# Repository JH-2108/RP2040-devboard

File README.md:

# Small devboard 

A custom RP2040-based development board designed from scratch in KiCAD as part of Hack Club Half Life. 

The DevBoard is a compact general-purpose development platform with native USB-C connectivity, external QSPI flash, 3.3V power regulation, GPIO breakout, onboard controls, and a status LED. The board is intended to be used for embedded programming, electronics experimentation, robotics, sensors, displays, and future hardware projects. 

# Features 
- Raspberry Pi RP2040 microcontroller
- Native USB-C connectivity
- External QSPI flash
- 12 MHz crystal oscillator
- 3.3V power regulation
- 2x20 GPIO breakout pins
- BOOTSEL and RESET buttons
- Onboard status LED
- SMD components
- Custom PCB designed in KiCAD

# Hardware 
The board is built around the RP2040 and follows the required circuity for its power, clock, USB, and external flash interfaces. 

# Main components
- RP2040 MCU
- W25Q128 QSPI flash
- 12 MHz crystal
- USB-C connector
- 3.3V LDO regulator
- Decoupling and filtering capacitors
- USB-C CC resistors
- GPIO headers
- RESET and BOOTSEL buttons
- Status LED

# Firmware
The devboard will be programmed using the Raspberry Pi Pico SDK and C/C++. 

The initial firmware will provide: 
- RP2040 boot and initialization
- USB connectivity
- GPIO testing
- Status LED control
- Board diagnostics
- USB serial communication

A diagnostic firmware can be used to verify that the assembled PCB is functioning correctly. 

# PC software
A small optional Python utility may be developed to communicated with the board over USB serial. 

This can be used to 
- Display board information
- Run hardware tests
- Control the onboard LED
- Test GPIO
- Monitor diagnostic output

# Firmware flashing 
The devboard uses the RP2040 microcontroller chip. Compatible UF2 firmware can be flashed over USB without an external programmer, provided the board's USB interface and BOOTSEL circuit are functioning correctly. 

# Requirements
- A USB data cable compatible with the board's USB-C connector
- A computer running either Windows, macOS, or Linux
- A compatible .uf2 firmware file

# Instructions 
1. Obtain the firmware. Download a UF2 firmware file that is compatible with the RP2040 and the intended application. Alternatively, build the firmware from its source code using the appropriate development tools.
2. Enter BOOTSEL mode. Disconnect the devboard from USB. Press and hold the BOOTSEL button, then connect the board to the computer. Release the button after the computer detects the board.
3. Open the bootloader drive. The board should appear as a USB mass-storage device named RPI-RP2. If it does not appear, check the connecting cable, power supply, and BOOTSEL circuit.
4. Copy the firmware. Drag the compatible .uf2 file into the RPI-RP2 drive.
5. Wait for the installation to finish. The drive should disconnect automatically as the RP2040 reboots and begins running the newly installed firmware.
6. Test the board. Verify that the firmware behaves as expected. If the application exposes a USB serial interface, open a serial terminal to inspect its output.

# Troubleshooting 
- The drive does not appear: make sure your USB cable supports data, not just charging. Check that the board receives power and the BOOTSEL circuit is assembled correctly.
- The firmware is rejected or does not run: confirm that the UF2 file targets the RP2040 and is built for the board's memory layout and hardware.
- The board does not behave as expected: try a known-compatible firmware image and inspect the power supply, clock circuit (especially this one), flash connections, and USB data routing.

# Important Notes 
- A UF2 file must be compatible with the RP2040 and the target firmware cofiguration.
- Flashing new firmware replaces the existing application in flash memory.
- BOOTSEL mode is implemented in the RP2040's read-only boot ROM, so compatible hardware can normally re-enter the bootloader even if the installed application fails.
If all else does not work, see the official Raspberry Pi microcontroller chip documentation. 

# Design
The PCB and schematic are designed using KiCAD. 
Project files include: 
- Schematic
- PCB layout
- Component/footprint assignments
- BOM
- Manufacturing files

# Design process
1. select and verify components for pricing and whether it is within budget range
2. create the schematic
3. assign symbols and footprints
4. design the PCB layout
5. route the board
6. run electrical and design rule checks
7. generate gerber files
8. assemble the PCB
9. develop and test firmware
10. test the complete board

# Bill of Materials 
|Item|Qty                          |Supplier|Cost/item                                    |Total Cost|link                                                                                                                                                                                                                                               |
|----|-----------------------------|--------|---------------------------------------------|----------|---------------------------------------------------------------------------------------------------------------------------------------------------------------------------------------------------------------------------------------------------|
|Raspberry Pi RP2040CT|1                            |Cytron  |$1.15                                        |$1.15     |https://my.cytron.io/p-raspberry-pi-rp2040-mcu-ic-single-unit                                                                                                                                                                                      |
|Winbond W25Q128JVSIQ|1                            |LCSC    |$2.52                                        |$2.52     |https://www.lcsc.com/product-detail/C113767.html                                                                                                                                                                                                   |
|12 MHz SMD crystal, 3225 4-pin|5                            |LCSC    |$0.10                                        |$0.50     |https://www.lcsc.com/product-detail/C518158.html                                                                                                                                                                                                   |
|USB Type-C 16-pin receptacle|1                            |Shopee Malaysia|$0.65                                        |$0.65     |https://shopee.com.my/Type-C-3.1-Patch-Socket-6P-16P-24P-Countersunk-Board-1.6-0.8mm-USB-Female-Socket-Data-Interface-i.513412485.42610897264?extraParams=%7B%22display_model_id%22%3A260916036060%2C%22model_selection_logic%22%3A3%7D            |
|3.3 V LDO regulator|1                            |Shopee Malaysia|$0.46                                        |$0.46     |https://shopee.com.my/AMS1117-Voltage-Regulator-IC-SOT-223-1.2V-1.5V-1.8V-2.5V-3.3V-5V-i.1412281456.49416215365?extraParams=%7B%22display_model_id%22%3A396380238012%2C%22model_selection_logic%22%3A3%7D                                          |
|10 µF ceramic capacitor|1                            |Shopee Malaysia|$1.05                                        |$1.05     |https://shopee.com.my/50V-10uF-Multilayer-Capacitor-i.40459773.23082863550?extraParams=%7B%22display_model_id%22%3A138766713726%2C%22model_selection_logic%22%3A3%7D                                                                               |
|100 nF ceramic capacitor|1                            |Shopee Malaysia|$1.25                                        |$1.25     |https://shopee.com.my/0402-0603-0805-1206-100nF-820nF-SMD-Chip-Capacitor-i.1467039591.41834021222?extraParams=%7B%22display_model_id%22%3A218871594639%2C%22model_selection_logic%22%3A3%7D                                                        |
|5.1 kΩ resistor|1                            |Shopee Malaysia|$1.24                                        |$1.24     |https://shopee.com.my/SMD-0402-0603-0805-1206-RESISTOR-1K-9.1K-Ohm-i.1467039591.50009312017?extraParams=%7B%22display_model_id%22%3A307560786040%2C%22model_selection_logic%22%3A3%7D                                                              |
|1 kΩ resistor|1                            |Shopee Malaysia|$1.24                                        |$1.24     |https://shopee.com.my/SMD-0402-0603-0805-1206-RESISTOR-1K-9.1K-Ohm-i.1467039591.50009312017?extraParams=%7B%22display_model_id%22%3A307560786040%2C%22model_selection_logic%22%3A3%7D                                                              |
|0603 LED|1                            |Shopee Malaysia|$0.88                                        |$0.88     |https://shopee.com.my/SMD-0402-0603-0805-1206-RESISTOR-1K-9.1K-Ohm-i.1467039591.50009312017?extraParams=%7B%22display_model_id%22%3A307560786040%2C%22model_selection_logic%22%3A3%7D                                                              |
|Tactile push button|1                            |Shopee Malaysia|$0.31                                        |$0.31     |https://shopee.com.my/Button-Switch-Tactile-Push-6x6x5mm-6*6*5mm-4PIN-i.482535902.11217352127?extraParams=%7B%22display_model_id%22%3A100951846821%2C%22model_selection_logic%22%3A3%7D                                                            |
|Tactile push button|1                            |Shopee Malaysia|$0.31                                        |$0.31     |https://shopee.com.my/Button-Switch-Tactile-Push-6x6x5mm-6*6*5mm-4PIN-i.482535902.11217352127?extraParams=%7B%22display_model_id%22%3A100951846821%2C%22model_selection_logic%22%3A3%7D                                                            |
|2.54 mm male pin headers|1                            |Shopee Malaysia|$0.30                                        |$0.30     |https://shopee.com.my/Male-Header-Pins-Straight-Single-Row-40-Pin-0.1-Inch-(2.54mm)-Male-Pin-Header-Connector-PCB-Board-Pin-Connect-i.161803224.7025057004?extraParams=%7B%22display_model_id%22%3A21946244149%2C%22model_selection_logic%22%3A3%7D|
|Custom PCB|1                            |JLCPCB  |$5.78                                        |$5.78     |https://jlcpcb.com                                                                                                                                                                                                                                 |
|Estimated total shipping|1                            |        |                                             |$7.75     |                                                                                                                                                                                                                                                   
# Project goals
The main goal is to design and build a fully functioning custom development board rather than relying on an existing development board such as the Raspberry Pi Pico. 

The project combines: 
- PCB design
- embedded systems
- electronics
- Firmware development
- USB communication
- hardware testing
- software development

# project images

**Schematic** 

**PCB layout**

**3d Render**

**Finished PCB**
a photo will be added here 

# LICENSE
This project is licensed under MIT License, check out [LICENSE](LICENSE) for more details.

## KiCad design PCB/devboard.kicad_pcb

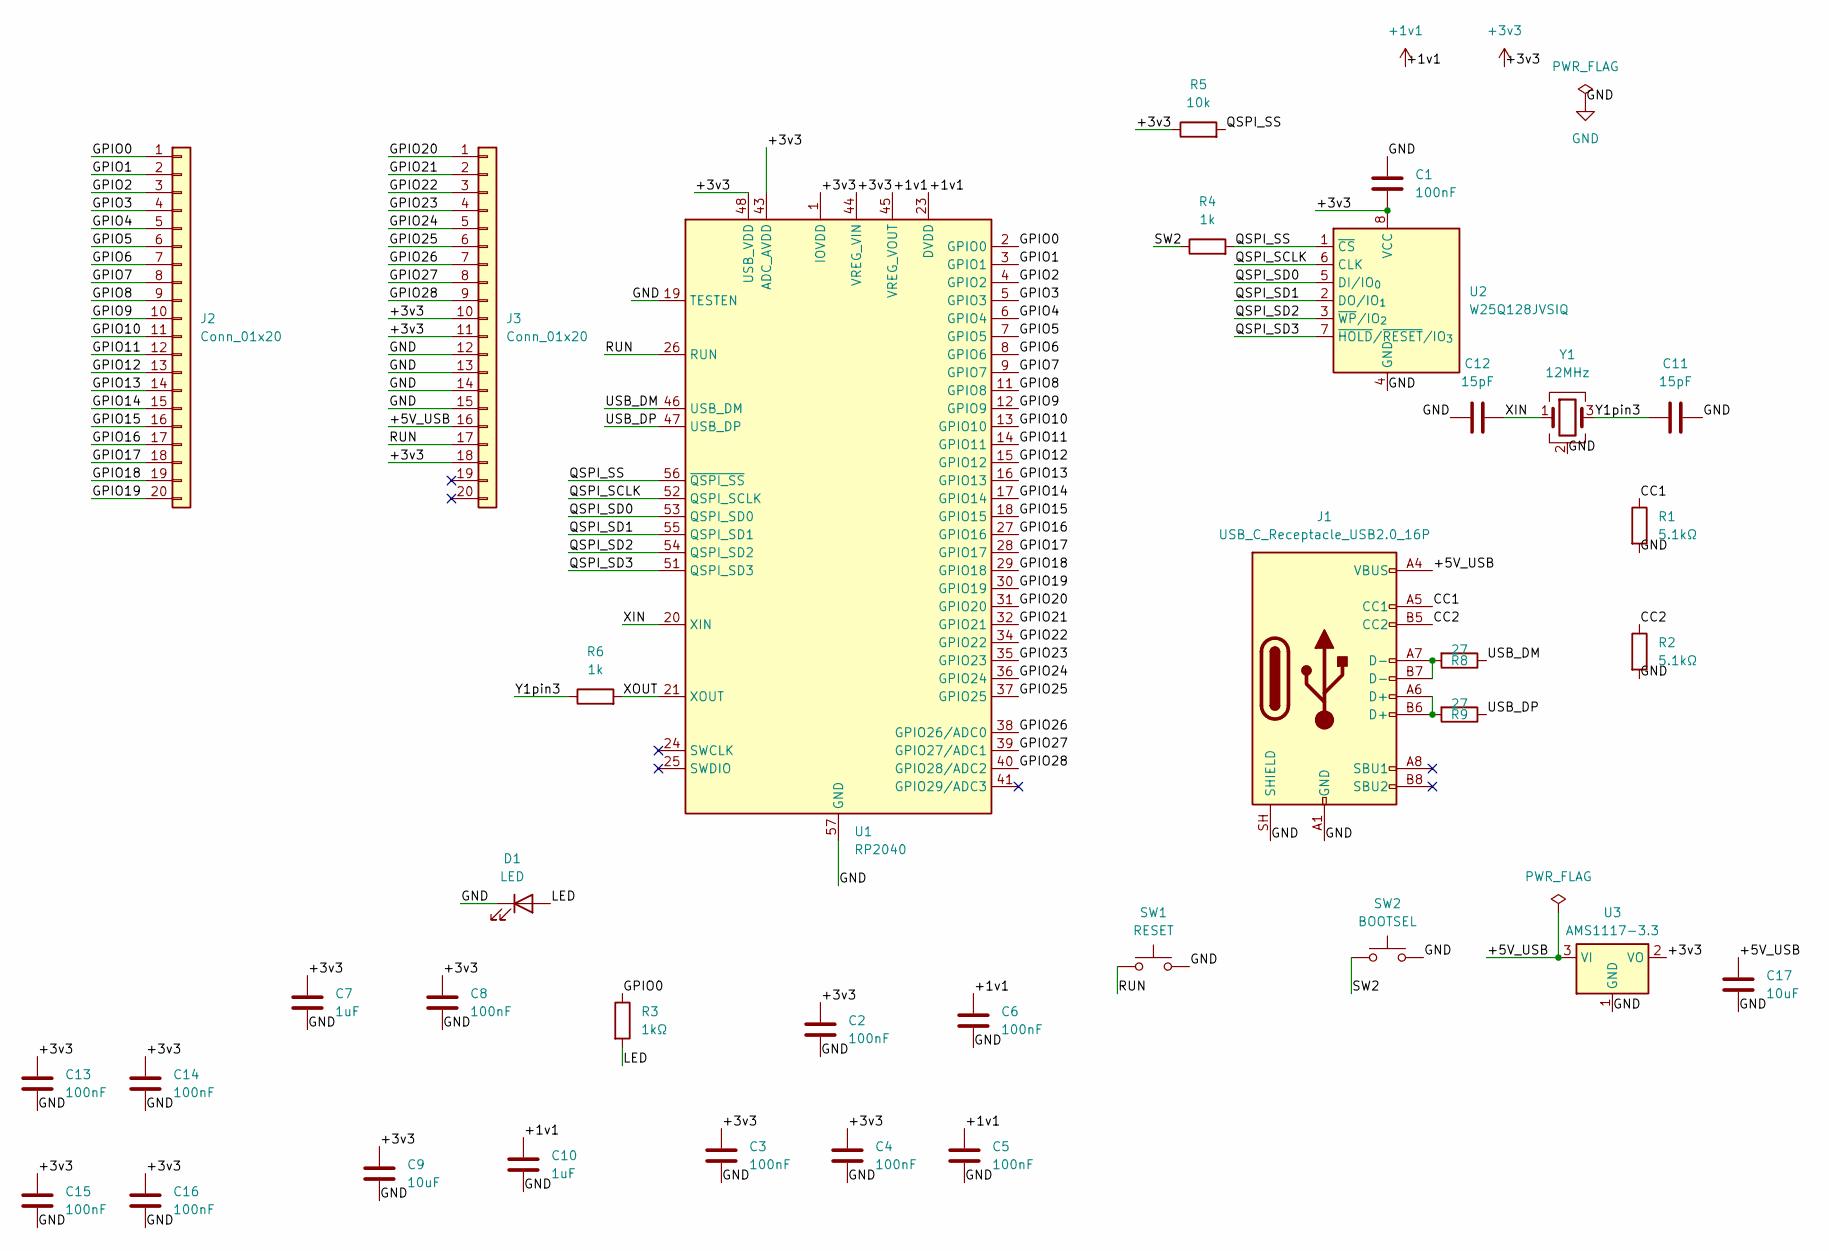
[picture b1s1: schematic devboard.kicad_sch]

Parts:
C1, C2, C3, C4, C5, C6, C8, C13, C14, C15, C16: 100nF; C_0603_1608Metric
C7, C10: 1uF; C_0603_1608Metric
C9, C17: 10uF; C_0603_1608Metric
C11, C12: 15pF; C_0603_1608Metric
D1: LED; LED_0603_1608Metric
J1: USB_C_Receptacle_USB2.0_16P; USB_C_Receptacle_GCT_USB4105-xx-A_16P_TopMnt_Horizontal
J2, J3: Conn_01x20; PinHeader_1x20_P2.54mm_Vertical
R1, R2: 5.1kΩ; R_0603_1608Metric
R3: 1kΩ; R_0603_1608Metric
R4, R6: 1k; R_0603_1608Metric
R5: 10k; R_0603_1608Metric
R8, R9: 27; R_0603_1608Metric
SW1: RESET; SW_Push_1P1T_NO_E-Switch_TL3301NxxxxxG
SW2: BOOTSEL; SW_Push_1P1T_NO_E-Switch_TL3301NxxxxxG
U1: RP2040; QFN-56-1EP_7x7mm_P0.4mm_EP3.2x3.2mm
U2: W25Q128JVSIQ; SOIC-8_5.3x5.3mm_P1.27mm
U3: AMS1117-3.3; SOT-223-3_TabPin2
Y1: 12MHz; Crystal_SMD_3225-4Pin_3.2x2.5mm

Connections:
+1v1: C5.1, C6.1, C10.1, U1.23 (DVDD), U1.45 (VREG_VOUT), U1.50 (DVDD)
+3v3: C1.2, C2.1, C3.1, C4.1, C7.1, C8.1, C9.1, C13.1, C14.1, C15.1, C16.1, J3.10, J3.11, J3.18, R5.1, U1.1 (IOVDD), U1.10 (IOVDD), U1.22 (IOVDD), U1.33 (IOVDD), U1.42 (IOVDD), U1.43 (ADC_AVDD), U1.44 (VREG_VIN), U1.48 (USB_VDD), U1.49 (IOVDD), U2.8 (VCC), U3.2 (VO)
/+5V_USB: C17.1, J1.A4 (VBUS), J1.A9 (VBUS), J1.B4 (VBUS), J1.B9 (VBUS), J3.16, U3.3 (VI)
/CC1: J1.A5 (CC1), R1.1
/CC2: J1.B5 (CC2), R2.1
/GPIO0: J2.1, R3.1, U1.2 (GPIO0)
/GPIO1: J2.2, U1.3 (GPIO1)
/GPIO2: J2.3, U1.4 (GPIO2)
/GPIO3: J2.4, U1.5 (GPIO3)
/GPIO4: J2.5, U1.6 (GPIO4)
/GPIO5: J2.6, U1.7 (GPIO5)
/GPIO6: J2.7, U1.8 (GPIO6)
/GPIO7: J2.8, U1.9 (GPIO7)
/GPIO8: J2.9, U1.11 (GPIO8)
/GPIO9: J2.10, U1.12 (GPIO9)
/GPIO10: J2.11, U1.13 (GPIO10)
/GPIO11: J2.12, U1.14 (GPIO11)
/GPIO12: J2.13, U1.15 (GPIO12)
/GPIO13: J2.14, U1.16 (GPIO13)
/GPIO14: J2.15, U1.17 (GPIO14)
/GPIO15: J2.16, U1.18 (GPIO15)
/GPIO16: J2.17, U1.27 (GPIO16)
/GPIO17: J2.18, U1.28 (GPIO17)
/GPIO18: J2.19, U1.29 (GPIO18)
/GPIO19: J2.20, U1.30 (GPIO19)
/GPIO20: J3.1, U1.31 (GPIO20)
/GPIO21: J3.2, U1.32 (GPIO21)
/GPIO22: J3.3, U1.34 (GPIO22)
/GPIO23: J3.4, U1.35 (GPIO23)
/GPIO24: J3.5, U1.36 (GPIO24)
/GPIO25: J3.6, U1.37 (GPIO25)
/GPIO26: J3.7, U1.38 (GPIO26/ADC0)
/GPIO27: J3.8, U1.39 (GPIO27/ADC1)
/GPIO28: J3.9, U1.40 (GPIO28/ADC2)
/LED: D1.2 (A), R3.2
/QSPI_SCLK: U1.52 (QSPI_SCLK), U2.6 (CLK)
/QSPI_SD0: U1.53 (QSPI_SD0), U2.5 (DI/IO_{0})
/QSPI_SD1: U1.55 (QSPI_SD1), U2.2 (DO/IO_{1})
/QSPI_SD2: U1.54 (QSPI_SD2), U2.3 (~WP/IO_{2})
/QSPI_SD3: U1.51 (QSPI_SD3), U2.7 (~HOLD/~RESET/IO_{3})
/QSPI_SS: R4.2, R5.2, U1.56 (~QSPI_SS), U2.1 (~CS)
/RUN: J3.17, SW1.1, U1.26 (RUN)
/SW2: R4.1, SW2.1
/USB_DM: R8.1, U1.46 (USB_DM)
/USB_DP: R9.1, U1.47 (USB_DP)
/XIN: C12.2, U1.20 (XIN), Y1.1
/XOUT: R6.2, U1.21 (XOUT)
/Y1pin3: C11.1, R6.1, Y1.3
GND: C1.1, C2.2, C3.2, C4.2, C5.2, C6.2, C7.2, C8.2, C9.2, C10.2, C11.2, C12.1, C13.2, C14.2, C15.2, C16.2, C17.2, D1.1 (K), J1.A1 (GND), J1.A12 (GND), J1.B1 (GND), J1.B12 (GND), J1.SH (SHIELD), J3.12, J3.13, J3.14, J3.15, R1.2, R2.2, SW1.2, SW2.2, U1.19 (TESTEN), U1.57 (GND), U2.4 (GND), U3.1 (GND), Y1.2 (G), Y1.4 (G)
unnamed: J1.A6 (D+), J1.B6 (D+), R9.2
unnamed: J1.A7 (D-), J1.B7 (D-), R8.2

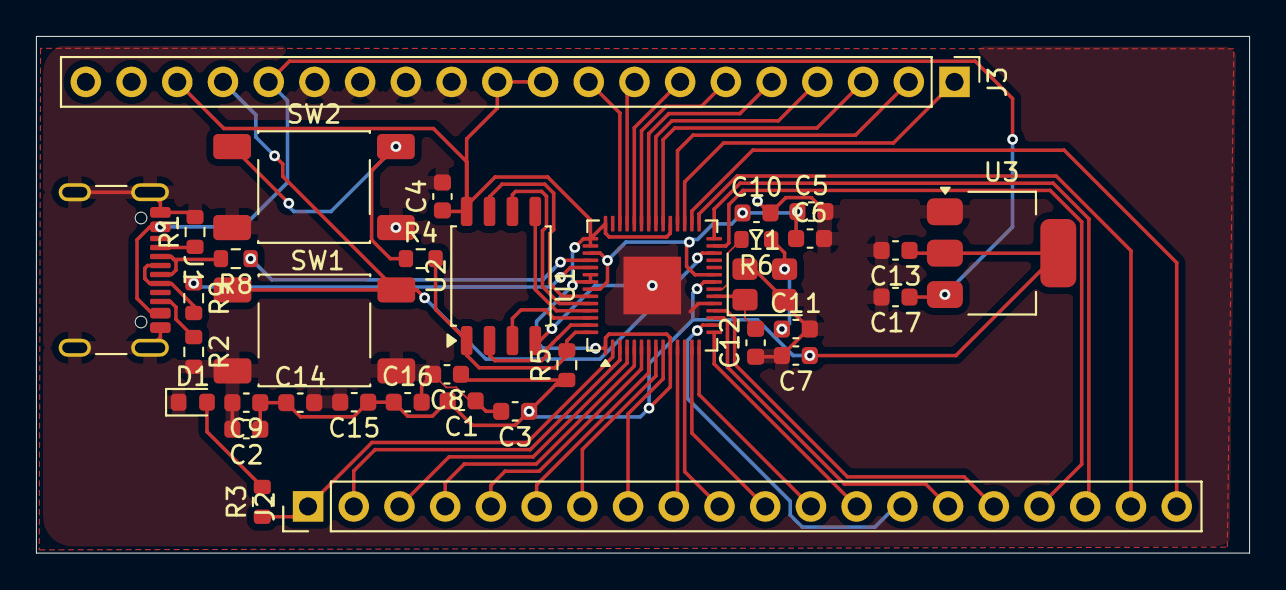
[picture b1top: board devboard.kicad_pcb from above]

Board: 2 copper layers, 67.4 x 28.7 mm, 35 parts (0 on the bottom side), 51 nets.

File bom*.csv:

"Reference","Qty","Value","DNP","Exclude from BOM","Exclude from Board","Exclude from Simulation","Exclude from Position Files","Footprint","Datasheet"
"C1,C2,C3,C4,C5,C6,C8","7","100nF","","","","","${EXCLUDE_FROM_POS_FILES}","Capacitor_SMD:C_0603_1608Metric",""
"C7","1","1uF","","","","","${EXCLUDE_FROM_POS_FILES}","Capacitor_SMD:C_0603_1608Metric",""
"C9","1","10uF","","","","","${EXCLUDE_FROM_POS_FILES}","Capacitor_SMD:C_0603_1608Metric",""
"D1","1","LED","","","","","${EXCLUDE_FROM_POS_FILES}","LED_SMD:LED_0603_1608Metric",""
"J1","1","USB_C_Receptacle_USB2.0_16P","","","","","${EXCLUDE_FROM_POS_FILES}","Connector_USB:USB_C_Receptacle_GCT_USB4105-xx-A_16P_TopMnt_Horizontal","https://www.usb.org/sites/default/files/documents/usb_type-c.zip"
"J2,J3","2","Conn_01x20","","","","","${EXCLUDE_FROM_POS_FILES}","Connector_PinHeader_2.54mm:PinHeader_1x20_P2.54mm_Vertical",""
"R1,R2","2","5.1kΩ","","","","","${EXCLUDE_FROM_POS_FILES}","Resistor_SMD:R_0603_1608Metric",""
"R3","1","1kΩ","","","","","${EXCLUDE_FROM_POS_FILES}","Resistor_SMD:R_0603_1608Metric",""
"SW1","1","RESET","","","","","${EXCLUDE_FROM_POS_FILES}","Button_Switch_SMD:SW_Push_1P1T_NO_E-Switch_TL3301NxxxxxG",""
"SW2","1","BOOTSEL","","","","","${EXCLUDE_FROM_POS_FILES}","Button_Switch_SMD:SW_Push_1P1T_NO_E-Switch_TL3301NxxxxxG",""
"U1","1","RP2040","","","","","${EXCLUDE_FROM_POS_FILES}","Package_DFN_QFN:QFN-56-1EP_7x7mm_P0.4mm_EP3.2x3.2mm","https://datasheets.raspberrypi.com/rp2040/rp2040-datasheet.pdf"
"U2","1","W25Q128JVSIQ","","","","","${EXCLUDE_FROM_POS_FILES}","Package_SO:SOIC-8_5.3x5.3mm_P1.27mm","https://www.winbond.com/resource-files/w25q128jv_dtr%20revc%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"
"U3","1","AMS1117","","","","","${EXCLUDE_FROM_POS_FILES}","Package_TO_SOT_SMD:SOT-223-3_TabPin2","http://www.advanced-monolithic.com/pdf/ds1117.pdf"
"Y1","1","12MHz","","","","","${EXCLUDE_FROM_POS_FILES}","Crystal:Crystal_SMD_3225-4Pin_3.2x2.5mm",""
